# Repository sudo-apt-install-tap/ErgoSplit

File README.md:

<div align="center">

<br>

<h1>
  <b>
    ErgoSplit 
  </b> 
</h1>

<h3> <b> A low-profile split-keyboard! </b> </h1>

</div>

## **Overview**

A split keyboard with a minimalist low profile design!! Symmetrical for easy printing.

### Why?
I wanted a split keyboard thats low profile and looks cool

### How?
Use the firmware in [FIRMWARE](https://github.com/sudo-apt-install-tap/ErgoSplit/tree/main/FIRMWARE) . I've used circuitpy and kmk to do it!

## CAD
CAD files are available at [CAD](https://cad.onshape.com/documents/b054daab3e6eb83ef3a9c97b/w/872555f6aab0d85ae4c614f8/e/704b399ae3f1c5f397311600?renderMode=1&tangentEdgeStyle=2&uiState=69acfbf36f602ba6f013c85b)

## Images
<div align="center">

<br> Full render<br>

---

<br> PCB

---

<br> Left Sch

---

<br> Right Sch

### Build Images

Left Build!

Right Build!

Togather!

### VIDEO
[title](https://youtu.be/x2c1Rt32prMl)

## BOM

Name	| Quantity |	Price ( 1 UNIT) |	Price Total |	Runing Total | Link
-------|-------|-------|-------|-------|-------
MCU |	2 |	₹1,160.00 |	₹2,320.00 |	₹2,320.00 |	https://robu.in/product/seeed-studio-xiao-ble-nrf52840/
DIODES |	40 |	₹1.05 |	₹42.00 |	₹2,362.00 |	https://robu.in/product/mm1z27-slkor-sod-123-zener-diodes-rohs/
Hotswap Socket (Pack of 10) |	4 |	145 | 	₹580.00 |	₹2,942.00 |	https://neomacro.in/products/kailh-choc-pg1350-hot-swap-sockets?variant=48049369907478
Kailh Choc V1 (Pack of 10) |	4 |	₹480.00 |	₹1,920.00 |	₹4,862.00 |	https://neomacro.in/products/kailh-choc-v1-switches?variant=48049336025366
Keycaps 1U (Pack of 10) |	4 |	₹350.00 |	₹1,400.00 |	₹6,262.00 |	https://neomacro.in/products/chocfox-cfx-choc-blank-keycaps?variant=50664114913558
Homing Keys (Pack of 2) |	1 |	₹70.00 |	₹70.00 |	₹6,332.00 |	https://neomacro.in/products/chocfox-cfx-choc-blank-keycaps?variant=48049351590166
PCB |	5 |	₹470.00 |	₹2,350.00 |	₹8,682.00 |	https://jlcpcb.com/
Total |	--- |	---	| --- |	₹8,682.00	| ---
Round off total				~ 8.75k INR

### Total: $95
### Print Legion Shipping: $5
### Grand Total: $100

</div>

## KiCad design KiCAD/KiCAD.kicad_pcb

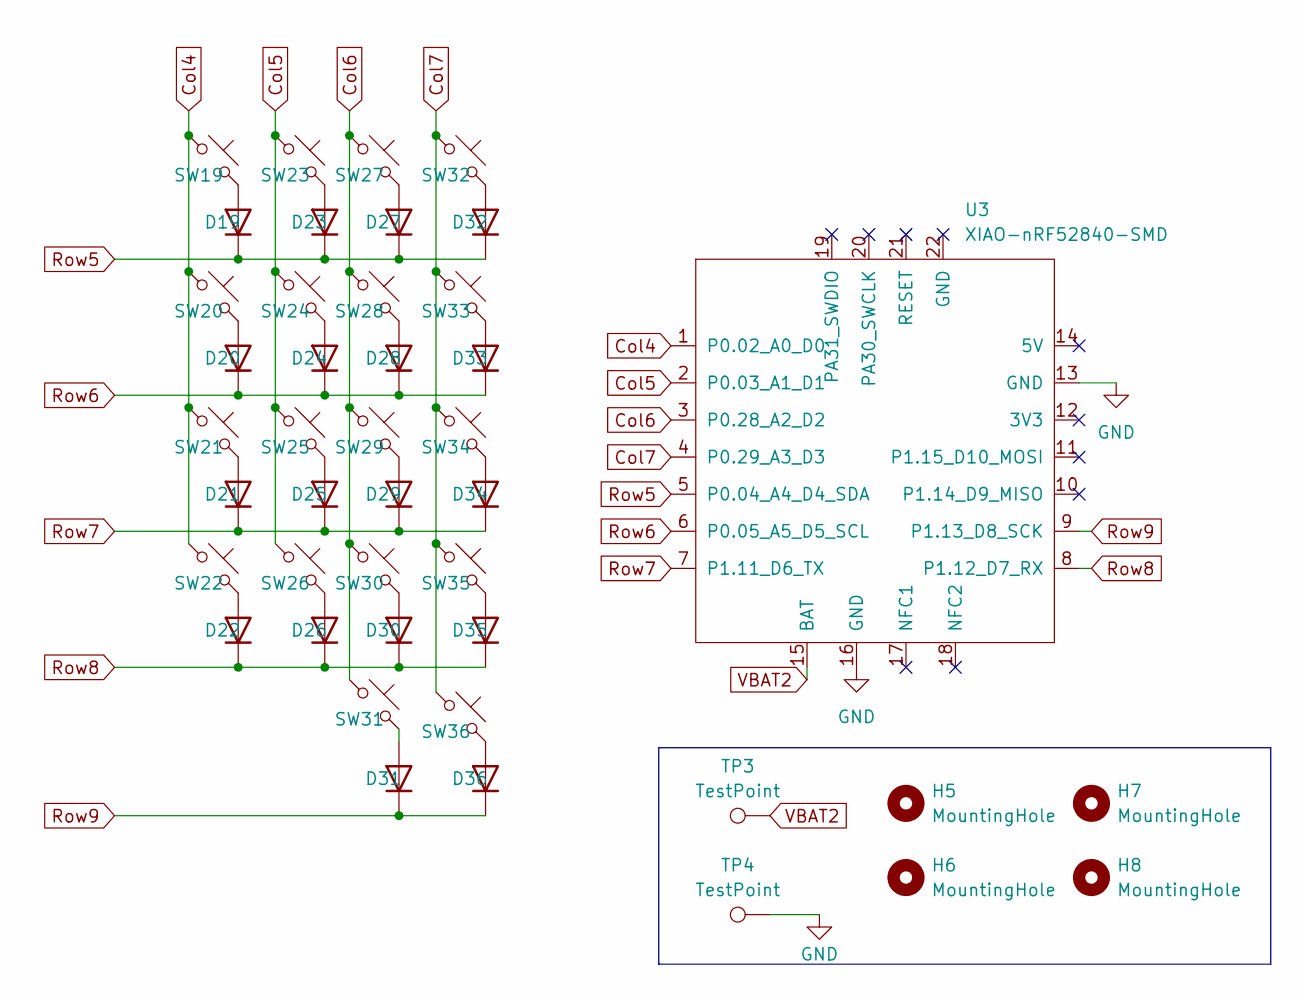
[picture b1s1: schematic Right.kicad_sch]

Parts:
D19, D20, D21, D22, D23, D24, D25, D26, D27, D28, D29, D30, D31, D32, D33, D34, D35, D36: D; D_SOD-123
H5, H6, H7, H8: MountingHole; MountingHole_2.2mm_M2
SW19, SW20, SW21, SW22, SW23, SW24, SW25, SW26, SW27, SW28, SW29, SW30, SW31, SW32, SW33, SW34, SW35, SW36: SW_Push_45deg; SW_Hotswap_Kailh_Choc_V1
TP3, TP4: TestPoint; TestPoint_Pad_D2.0mm
U3: XIAO-nRF52840-SMD

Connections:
Col4: SW19.1, SW20.1, SW21.1, SW22.1, U3.1 (P0.02_A0_D0)
Col5: SW23.1, SW24.1, SW25.1, SW26.1, U3.2 (P0.03_A1_D1)
Col6: SW27.1, SW28.1, SW29.1, SW30.1, SW31.1, U3.3 (P0.28_A2_D2)
Col7: SW32.1, SW33.1, SW34.1, SW35.1, SW36.1, U3.4 (P0.29_A3_D3)
GND: TP4.1, U3.13 (GND), U3.16 (GND); also elsewhere on the board
unnamed: D19.2 (A), SW19.2
unnamed: D20.2 (A), SW20.2
unnamed: D21.2 (A), SW21.2
unnamed: D22.2 (A), SW22.2
unnamed: D23.2 (A), SW23.2
unnamed: D24.2 (A), SW24.2
unnamed: D25.2 (A), SW25.2
unnamed: D26.2 (A), SW26.2
unnamed: D27.2 (A), SW27.2
unnamed: D28.2 (A), SW28.2
unnamed: D29.2 (A), SW29.2
unnamed: D30.2 (A), SW30.2
unnamed: D31.2 (A), SW31.2
unnamed: D32.2 (A), SW32.2
unnamed: D33.2 (A), SW33.2
unnamed: D34.2 (A), SW34.2
unnamed: D35.2 (A), SW35.2
unnamed: D36.2 (A), SW36.2
Row5: D19.1 (K), D23.1 (K), D27.1 (K), D32.1 (K), U3.5 (P0.04_A4_D4_SDA)
Row6: D20.1 (K), D24.1 (K), D28.1 (K), D33.1 (K), U3.6 (P0.05_A5_D5_SCL)
Row7: D21.1 (K), D25.1 (K), D29.1 (K), D34.1 (K), U3.7 (P1.11_D6_TX)
Row8: D22.1 (K), D26.1 (K), D30.1 (K), D35.1 (K), U3.8 (P1.12_D7_RX)
Row9: D31.1 (K), D36.1 (K), U3.9 (P1.13_D8_SCK)
VBAT2: TP3.1, U3.15 (BAT); also elsewhere on the board

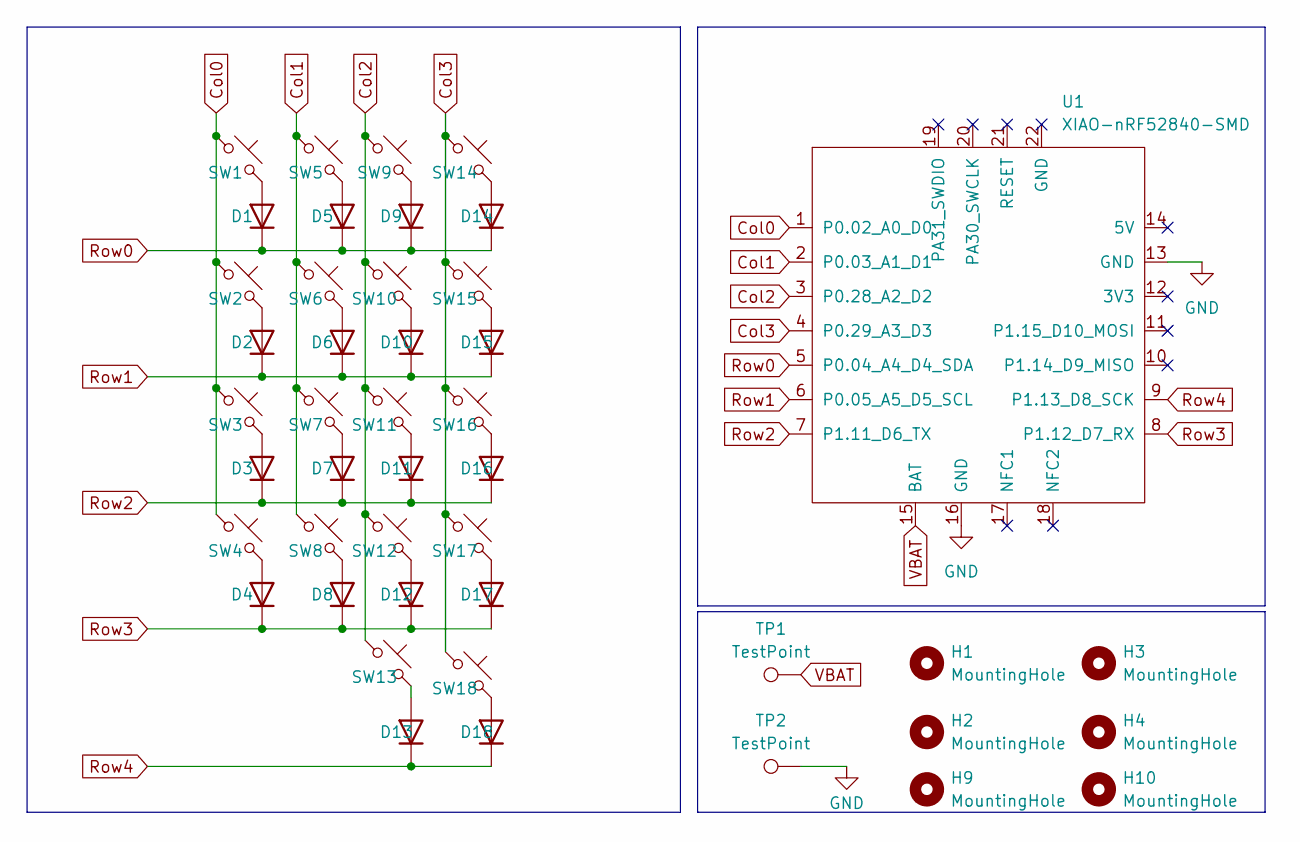
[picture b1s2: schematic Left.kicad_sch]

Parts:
D1, D2, D3, D4, D5, D6, D7, D8, D9, D10, D11, D12, D13, D14, D15, D16, D17, D18: D; D_SOD-123
H1, H2, H3, H4, H9, H10: MountingHole; MountingHole_2.2mm_M2
SW1, SW2, SW3, SW4, SW5, SW6, SW7, SW8, SW9, SW10, SW11, SW12, SW13, SW14, SW15, SW16, SW17, SW18: SW_Push_45deg; SW_Hotswap_Kailh_Choc_V1
TP1, TP2: TestPoint; TestPoint_Pad_D2.0mm
U1: XIAO-nRF52840-SMD

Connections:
Col0: SW1.1, SW2.1, SW3.1, SW4.1, U1.1 (P0.02_A0_D0)
Col1: SW5.1, SW6.1, SW7.1, SW8.1, U1.2 (P0.03_A1_D1)
Col2: SW9.1, SW10.1, SW11.1, SW12.1, SW13.1, U1.3 (P0.28_A2_D2)
Col3: SW14.1, SW15.1, SW16.1, SW17.1, SW18.1, U1.4 (P0.29_A3_D3)
GND: TP2.1, U1.13 (GND), U1.16 (GND); also elsewhere on the board
unnamed: D1.2 (A), SW1.2
unnamed: D2.2 (A), SW2.2
unnamed: D3.2 (A), SW3.2
unnamed: D4.2 (A), SW4.2
unnamed: D5.2 (A), SW5.2
unnamed: D6.2 (A), SW6.2
unnamed: D7.2 (A), SW7.2
unnamed: D8.2 (A), SW8.2
unnamed: D9.2 (A), SW9.2
unnamed: D10.2 (A), SW10.2
unnamed: D11.2 (A), SW11.2
unnamed: D12.2 (A), SW12.2
unnamed: D13.2 (A), SW13.2
unnamed: D14.2 (A), SW14.2
unnamed: D15.2 (A), SW15.2
unnamed: D16.2 (A), SW16.2
unnamed: D17.2 (A), SW17.2
unnamed: D18.2 (A), SW18.2
Row0: D1.1 (K), D5.1 (K), D9.1 (K), D14.1 (K), U1.5 (P0.04_A4_D4_SDA)
Row1: D2.1 (K), D6.1 (K), D10.1 (K), D15.1 (K), U1.6 (P0.05_A5_D5_SCL)
Row2: D3.1 (K), D7.1 (K), D11.1 (K), D16.1 (K), U1.7 (P1.11_D6_TX)
Row3: D4.1 (K), D8.1 (K), D12.1 (K), D17.1 (K), U1.8 (P1.12_D7_RX)
Row4: D13.1 (K), D18.1 (K), U1.9 (P1.13_D8_SCK)
VBAT: TP1.1, U1.15 (BAT); also elsewhere on the board

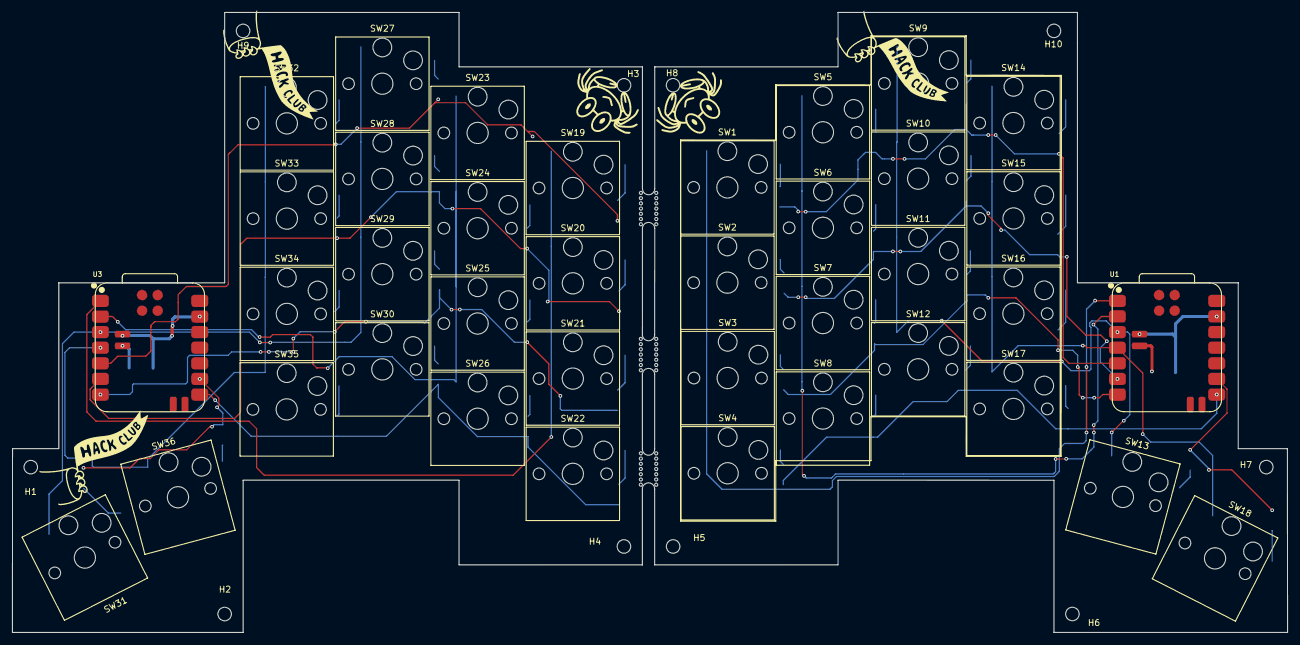
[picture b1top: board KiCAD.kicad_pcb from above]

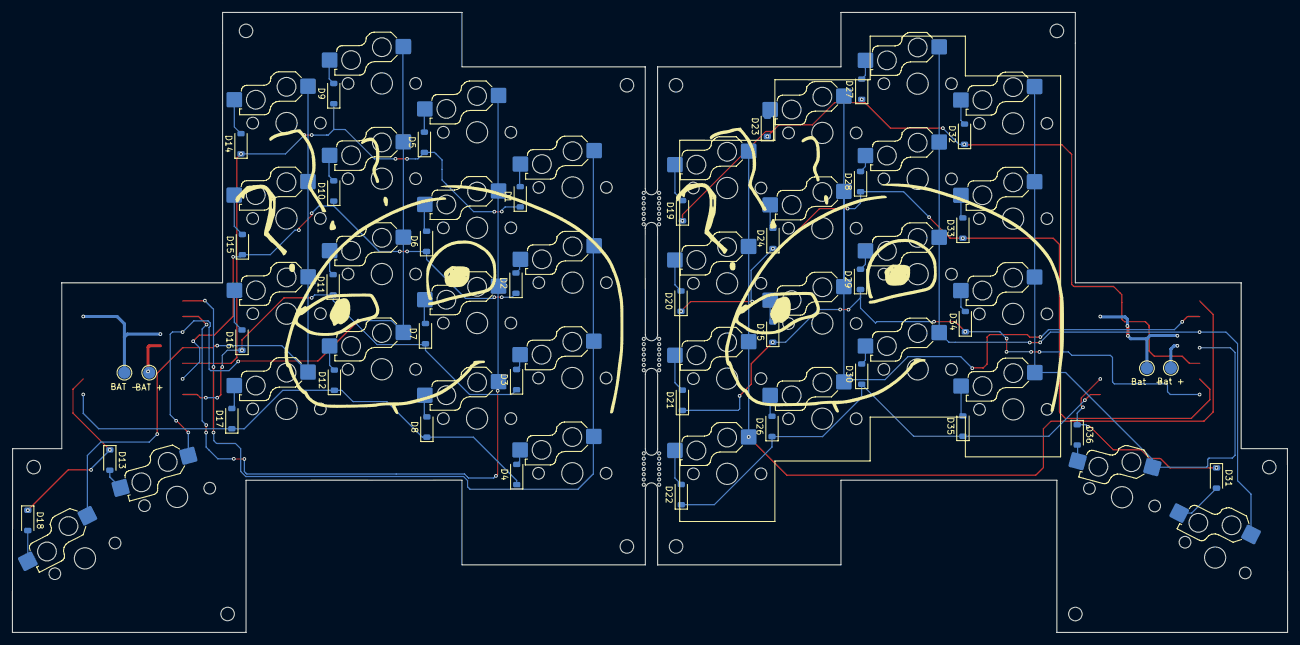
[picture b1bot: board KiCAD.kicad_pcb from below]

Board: 2 copper layers, 207.5 x 100.9 mm, 88 parts (40 on the bottom side), 57 nets.

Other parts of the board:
BAT +: TestPoint; TestPoint_Pad_D2.0mm
BAT -: TestPoint; TestPoint_Pad_D2.0mm
Bat  -: TestPoint; TestPoint_Pad_D2.0mm
Bat +: TestPoint; TestPoint_Pad_D2.0mm

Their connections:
GND: BAT -.1, Bat -.1; also elsewhere on the board
VBAT: BAT +.1; also elsewhere on the board
VBAT2: Bat +.1; also elsewhere on the board

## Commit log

2026-03-08 Create README.md for ErgoSplit project
    Added README.md with project overview, images, and links.
2026-03-08 Revise README.md with new sections and images
    Updated README.md to include additional content and formatting.
2026-03-08 Update README.md formatting and content
2026-03-08 Added BOM
2026-03-08 Update README with BOM and additional details
    Added detailed BOM with component links and pricing.
2026-03-08 Revise README with detailed project information
    Updated the README to include additional details about the ErgoSplit keyboard, including an overview, reasons for design choices, CAD file links, images, and a bill of materials (BOM).
2026-03-08 Added firmware for l and r
2026-03-08 Revise README for clarity and additional info
    Updated README.md to include additional details about the firmware used and corrected formatting issues.
2026-03-08 Update README with additional images and BOM details
2026-03-08 Added case stls
2026-03-11 Update README with formatted content and images
2026-03-11 Fix formatting issues in README.md
